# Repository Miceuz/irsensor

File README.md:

irsensor
========

Sensor array for line following robot

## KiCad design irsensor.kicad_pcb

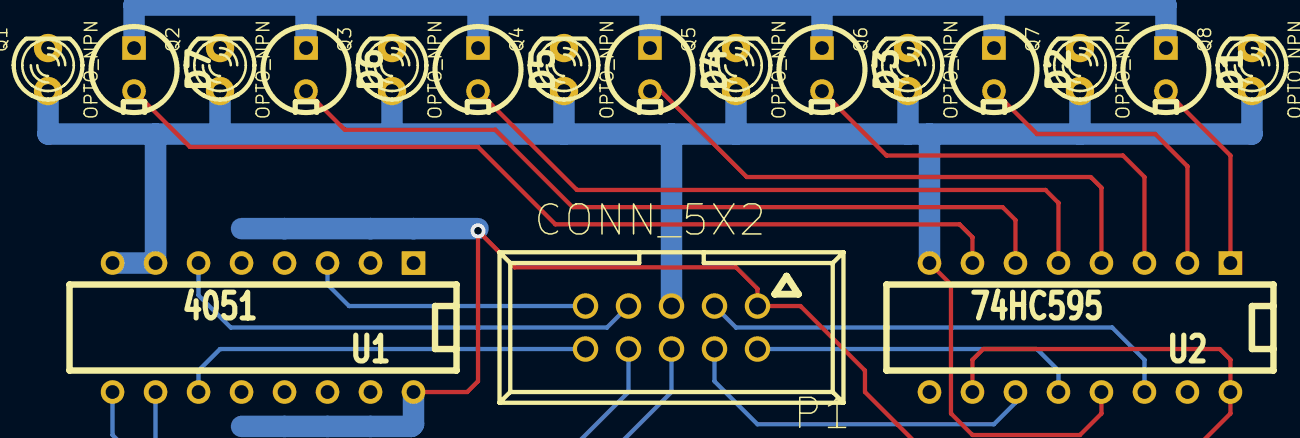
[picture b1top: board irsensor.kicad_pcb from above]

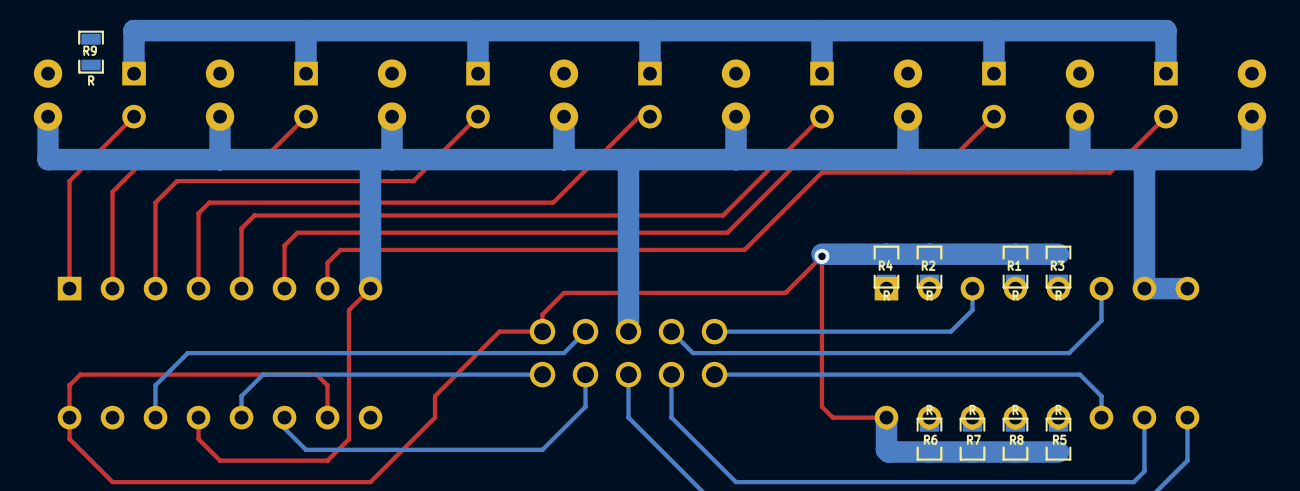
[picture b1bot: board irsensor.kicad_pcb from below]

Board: 2 copper layers, 27 parts (9 on the bottom side), 26 nets.

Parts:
D1, D2, D3, D4, D5, D6, D7: LED; LEDV
P1: CONN_5X2; VASCH5x2
Q1, Q2, Q3, Q4, Q5, Q6, Q7, Q8: OPTO_NPN; LED-3MM
R1, R2, R3, R4, R5, R6, R7, R8, R9: R; SM0603_Resistor
U1: 4051; DIP-16__300
U2: 74HC595; DIP-16__300

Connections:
/A: P1.10, U1.11
/B: P1.8, U1.10
/C: P1.6, U1.9
/CLK: P1.4, U2.11
/DATA: P1.3, U2.14
/LATCH: P1.2, U2.12
/MUX_OUT: P1.9, U1.3
/~MUX_E: P1.7, U1.6
GND: P1.5, Q1.1, Q2.1, Q3.1, Q4.1, Q5.1, Q6.1, Q7.1, Q8.1, U1.7, U1.8, U2.8, U2.13
unnamed: D6.2, U2.6
unnamed: D1.2, U2.1
unnamed: D2.2, U2.2
unnamed: D3.2, U2.3
unnamed: D4.2, U2.4
unnamed: D5.2, U2.5
unnamed: D7.2, U2.7
unnamed: Q3.3, R3.1, U1.5
unnamed: Q4.3, R4.1, U1.1
unnamed: Q5.3, R5.1, U1.12
unnamed: Q6.3, R6.1, U1.15
unnamed: Q7.3, R7.1, U1.14
unnamed: Q8.3, R8.1, U1.13
unnamed: Q1.3, R1.1, U1.4
unnamed: Q2.3, R2.1, U1.2
unnamed: D1.1, D2.1, D3.1, D4.1, D5.1, D6.1, D7.1, R9.2
VCC: P1.1, R1.2, R2.2, R3.2, R4.2, R5.2, R6.2, R7.2, R8.2, R9.1, U1.16, U2.10, U2.16

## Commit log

2013-12-15 initial
